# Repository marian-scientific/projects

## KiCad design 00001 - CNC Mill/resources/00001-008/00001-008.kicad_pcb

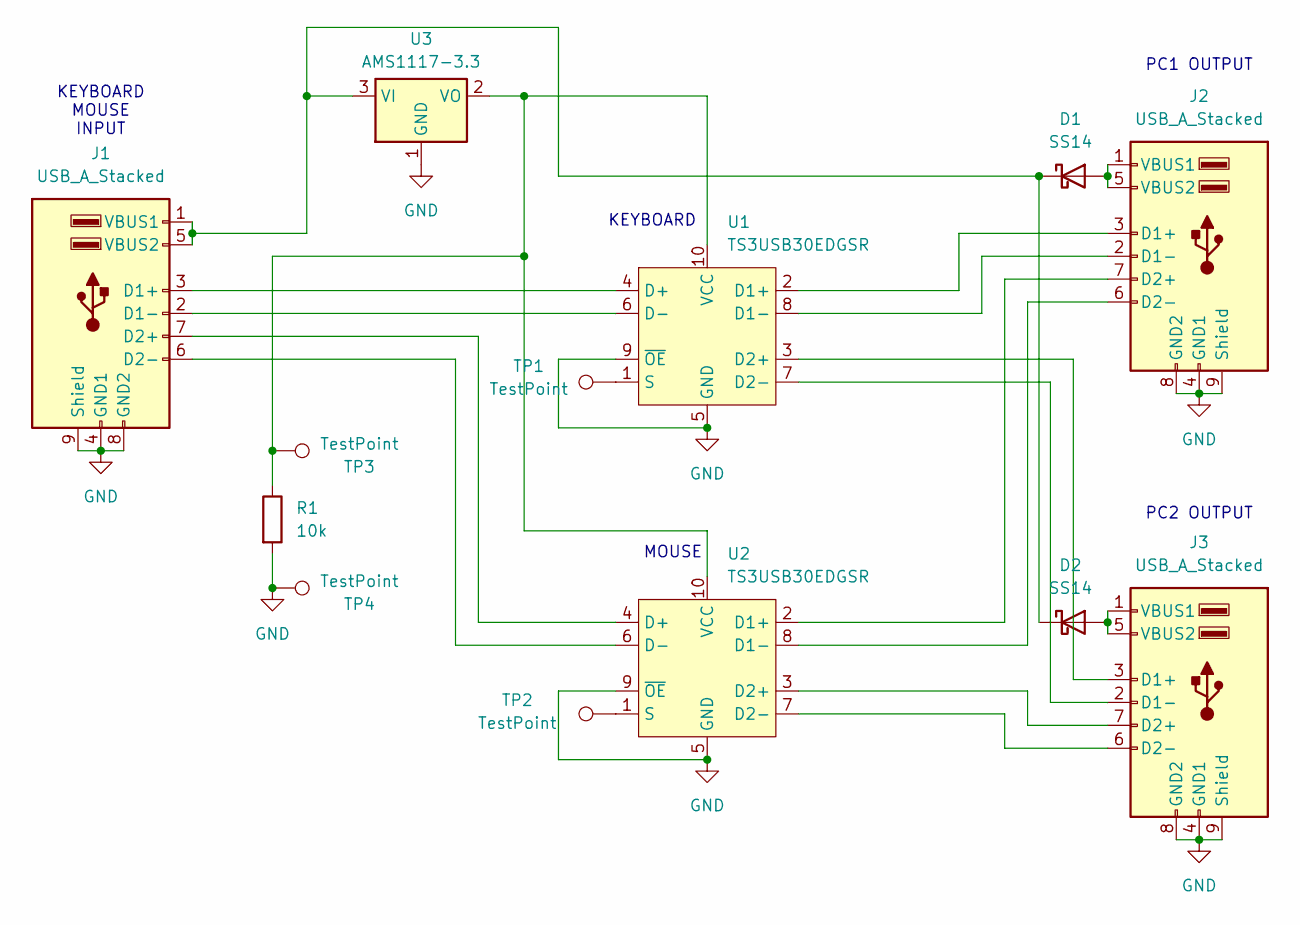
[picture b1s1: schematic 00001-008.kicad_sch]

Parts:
D1, D2: SS14; D_SMA
J1, J2, J3: USB_A_Stacked; USB_A_CUI_UJ2-ADH-TH_Horizontal_Stacked
R1: 10k; R_1206_3216Metric
TP1, TP2, TP3, TP4: TestPoint; TestPoint_Pad_3.0x3.0mm
U1, U2: TS3USB30EDGSR; VSSOP-10_3x3mm_P0.5mm
U3: AMS1117-3.3; SOT-223-3_TabPin2

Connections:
GND: J1.4 (GND1), J1.8 (GND2), J1.9 (Shield), J2.4 (GND1), J2.8 (GND2), J2.9 (Shield), J3.4 (GND1), J3.8 (GND2), J3.9 (Shield), R1.2, TP4.1, U1.5 (GND), U1.9 (~OE), U2.5 (GND), U2.9 (~OE), U3.1 (GND)
unnamed: D1.2 (A), J2.1 (VBUS1), J2.5 (VBUS2)
unnamed: D1.1 (K), D2.1 (K), J1.1 (VBUS1), J1.5 (VBUS2), U3.3 (VI)
unnamed: D2.2 (A), J3.1 (VBUS1), J3.5 (VBUS2)
unnamed: J1.3 (D1+), U1.4 (D+)
unnamed: J1.2 (D1-), U1.6 (D-)
unnamed: J1.7 (D2+), U2.4 (D+)
unnamed: J1.6 (D2-), U2.6 (D-)
unnamed: J2.3 (D1+), U1.2 (D1+)
unnamed: J2.2 (D1-), U1.8 (D1-)
unnamed: J2.7 (D2+), U2.2 (D1+)
unnamed: J2.6 (D2-), U2.8 (D1-)
unnamed: J3.3 (D1+), U1.3 (D2+)
unnamed: J3.2 (D1-), U1.7 (D2-)
unnamed: J3.7 (D2+), U2.3 (D2+)
unnamed: J3.6 (D2-), U2.7 (D2-)
unnamed: TP1.1, U1.1 (S)
unnamed: R1.1, TP3.1, U1.10 (VCC), U2.10 (VCC), U3.2 (VO)
unnamed: TP2.1, U2.1 (S)

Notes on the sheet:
PC1 OUTPUT
KEYBOARD MOUSE INPUT
PC2 OUTPUT
KEYBOARD
MOUSE

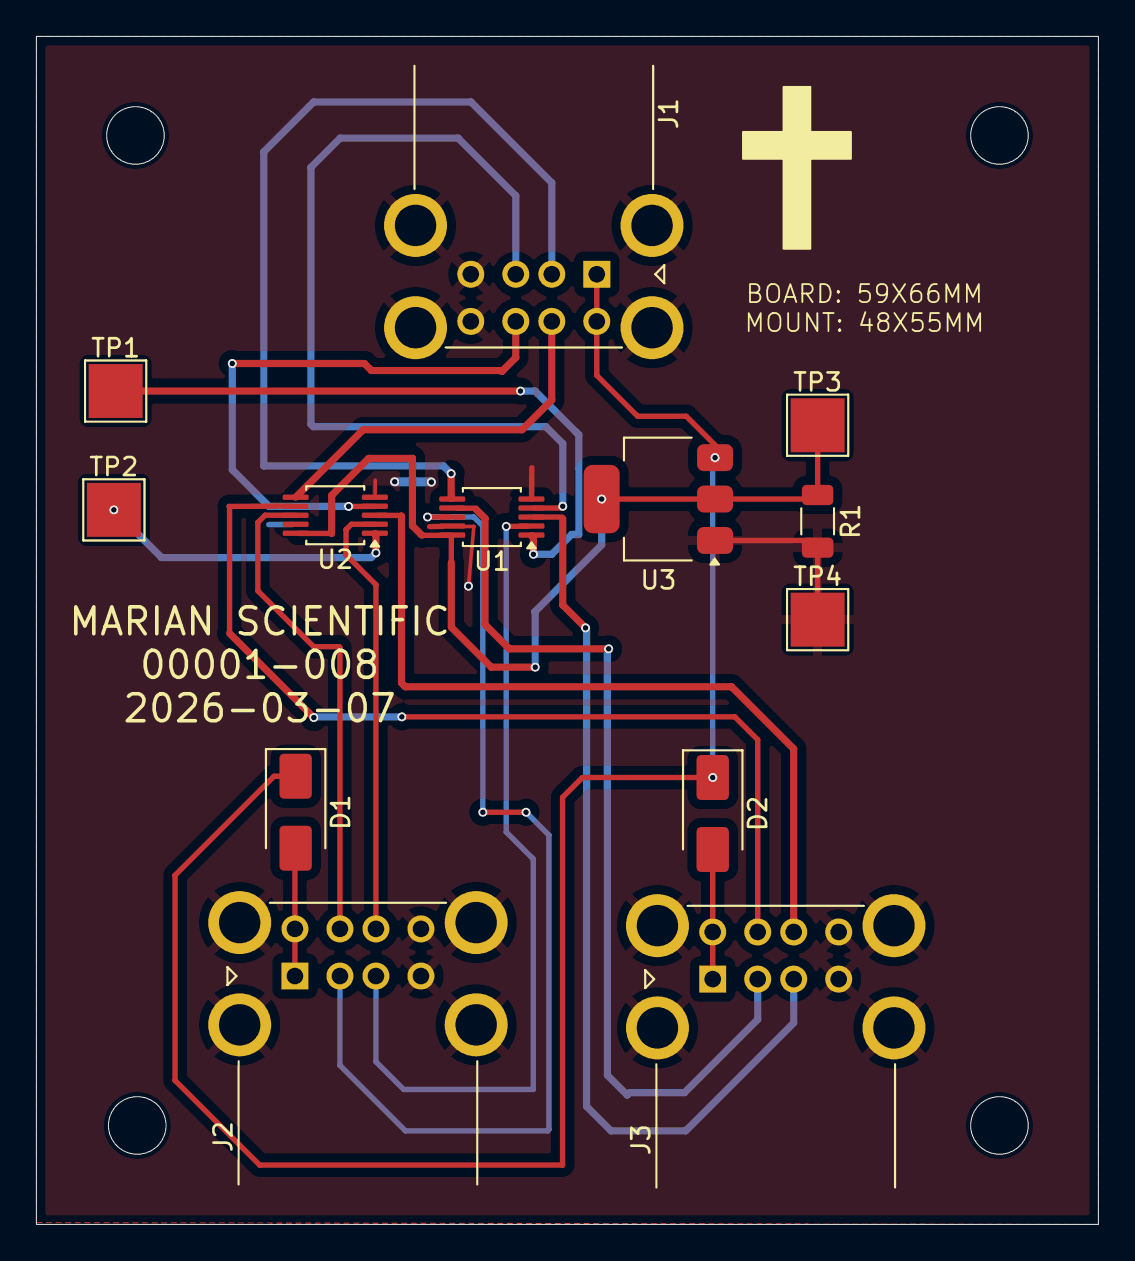
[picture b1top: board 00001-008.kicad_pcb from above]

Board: 2 copper layers, 59.0 x 66.0 mm, 13 parts (0 on the bottom side), 19 nets.

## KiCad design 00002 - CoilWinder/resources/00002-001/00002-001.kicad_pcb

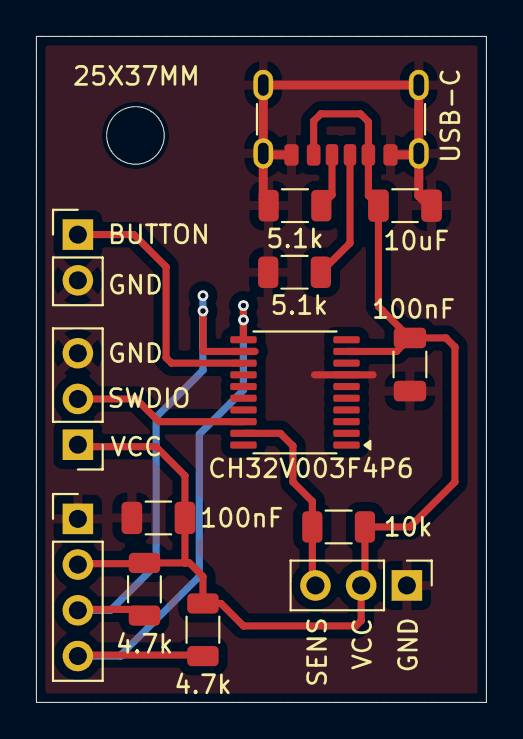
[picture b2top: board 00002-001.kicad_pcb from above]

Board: 2 copper layers, 25.0 x 37.0 mm, 14 parts (0 on the bottom side), 9 nets.

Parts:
4.7k, 4.7k#2: 4.7k; R_1206_3216Metric
5.1k, 5.1k#2: 5.1k; R_1206_3216Metric
10k: 10k; R_1206_3216Metric
10uF: 10uF; C_1206_3216Metric
100nF, 100nF#2: .1uF; C_1206_3216Metric
CH32V003F4P6: CH32V003FxPx; TSSOP-20_4.4x6.5mm_P0.65mm
J2: Conn_01x04_Pin; PinHeader_1x04_P2.54mm_Vertical
J3, J5: Conn_01x03_Pin; PinHeader_1x03_P2.54mm_Vertical
J4: Conn_01x02_Pin; PinHeader_1x02_P2.54mm_Vertical
USB-C: USB_C_Receptacle_PowerOnly_6P; USB_C_Receptacle_GCT_USB4125-xx-x_6P_TopMnt_Horizontal

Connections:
+5V: 4.7k.2, 4.7k#2.2, 10k.2, 10uF.1, 100nF.1, 100nF#2.1, CH32V003F4P6.9 (VDD), J2.2, J3.2, J5.1, USB-C.A9 (VBUS), USB-C.B9 (VBUS)
GND: 5.1k.2, 5.1k#2.2, 10uF.2, 100nF.2, 100nF#2.2, CH32V003F4P6.7 (VSS), J2.1, J3.1, J4.2, J5.3, USB-C.A12 (GND), USB-C.B12 (GND), USB-C.S1 (SHIELD)
unnamed: 5.1k.1, USB-C.A5 (CC1)
unnamed: 5.1k#2.1, USB-C.B5 (CC2)
unnamed: 4.7k#2.1, CH32V003F4P6.12 (PC2), J2.3
unnamed: 4.7k.1, CH32V003F4P6.11 (PC1), J2.4
unnamed: 10k.1, CH32V003F4P6.19 (PD2), J3.3
unnamed: CH32V003F4P6.13 (PC3), J4.1
unnamed: CH32V003F4P6.18 (PD1), J5.2

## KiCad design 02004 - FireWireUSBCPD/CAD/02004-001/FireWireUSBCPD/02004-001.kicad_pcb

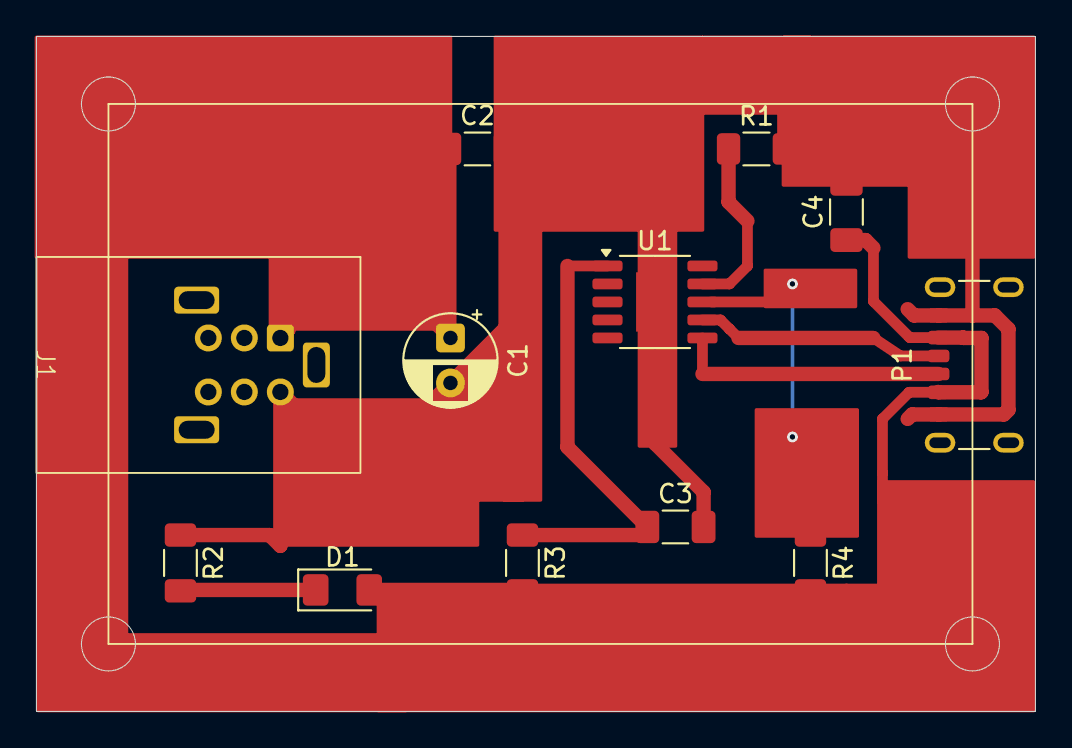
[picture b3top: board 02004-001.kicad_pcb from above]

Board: 2 copper layers, 55.5 x 37.5 mm, 12 parts (0 on the bottom side), 7 nets.

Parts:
C1: 22uF; CP_Radial_D5.0mm_P2.50mm
C2: 0.1uF; C_1206_3216Metric_Pad1.33x1.80mm_HandSolder
C3: 1uF; C_1206_3216Metric_Pad1.33x1.80mm_HandSolder
C4: 10uF; C_1206_3216Metric_Pad1.33x1.80mm_HandSolder
D1: LED; LED_1206_3216Metric_Pad1.42x1.75mm_HandSolder
J1: IEEE1394a; IEEE1394 930
P1: USB_C_Plug_USB2.0; USB_C_Receptacle_GCT_USB4125-xx-x_6P_TopMnt_Horizontal
R1: 56K; R_1206_3216Metric_Pad1.30x1.75mm_HandSolder
R2: 2K; R_1206_3216Metric_Pad1.30x1.75mm_HandSolder
R3: 1K; R_1206_3216Metric_Pad1.30x1.75mm_HandSolder
R4: 10K; R_1206_3216Metric_Pad1.30x1.75mm_HandSolder
U1: CH224K; SSOP-10-1EP_3.9x4.9mm_P1mm_EP2.1x3.3mm

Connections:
GND: C1.2, C2.2, C3.2, C4.2, J1.2 (GND), P1.A12 (GND), P1.B12 (GND), R1.2, R2.1, U1.11 (GND)
unnamed: C1.1, C2.1, C4.1, D1.2 (A), J1.1 (PWR), P1.A9 (VBUS), P1.B9 (VBUS), R3.2, R4.2
unnamed: D1.1 (K), R2.2
unnamed: P1.A5 (CC), U1.6 (CC2), U1.7 (CC1)
unnamed: R1.1, U1.9 (CFG1)
unnamed: R4.1, U1.8 (VBUS)
unnamed: C3.1, R3.1, U1.1 (VDD)

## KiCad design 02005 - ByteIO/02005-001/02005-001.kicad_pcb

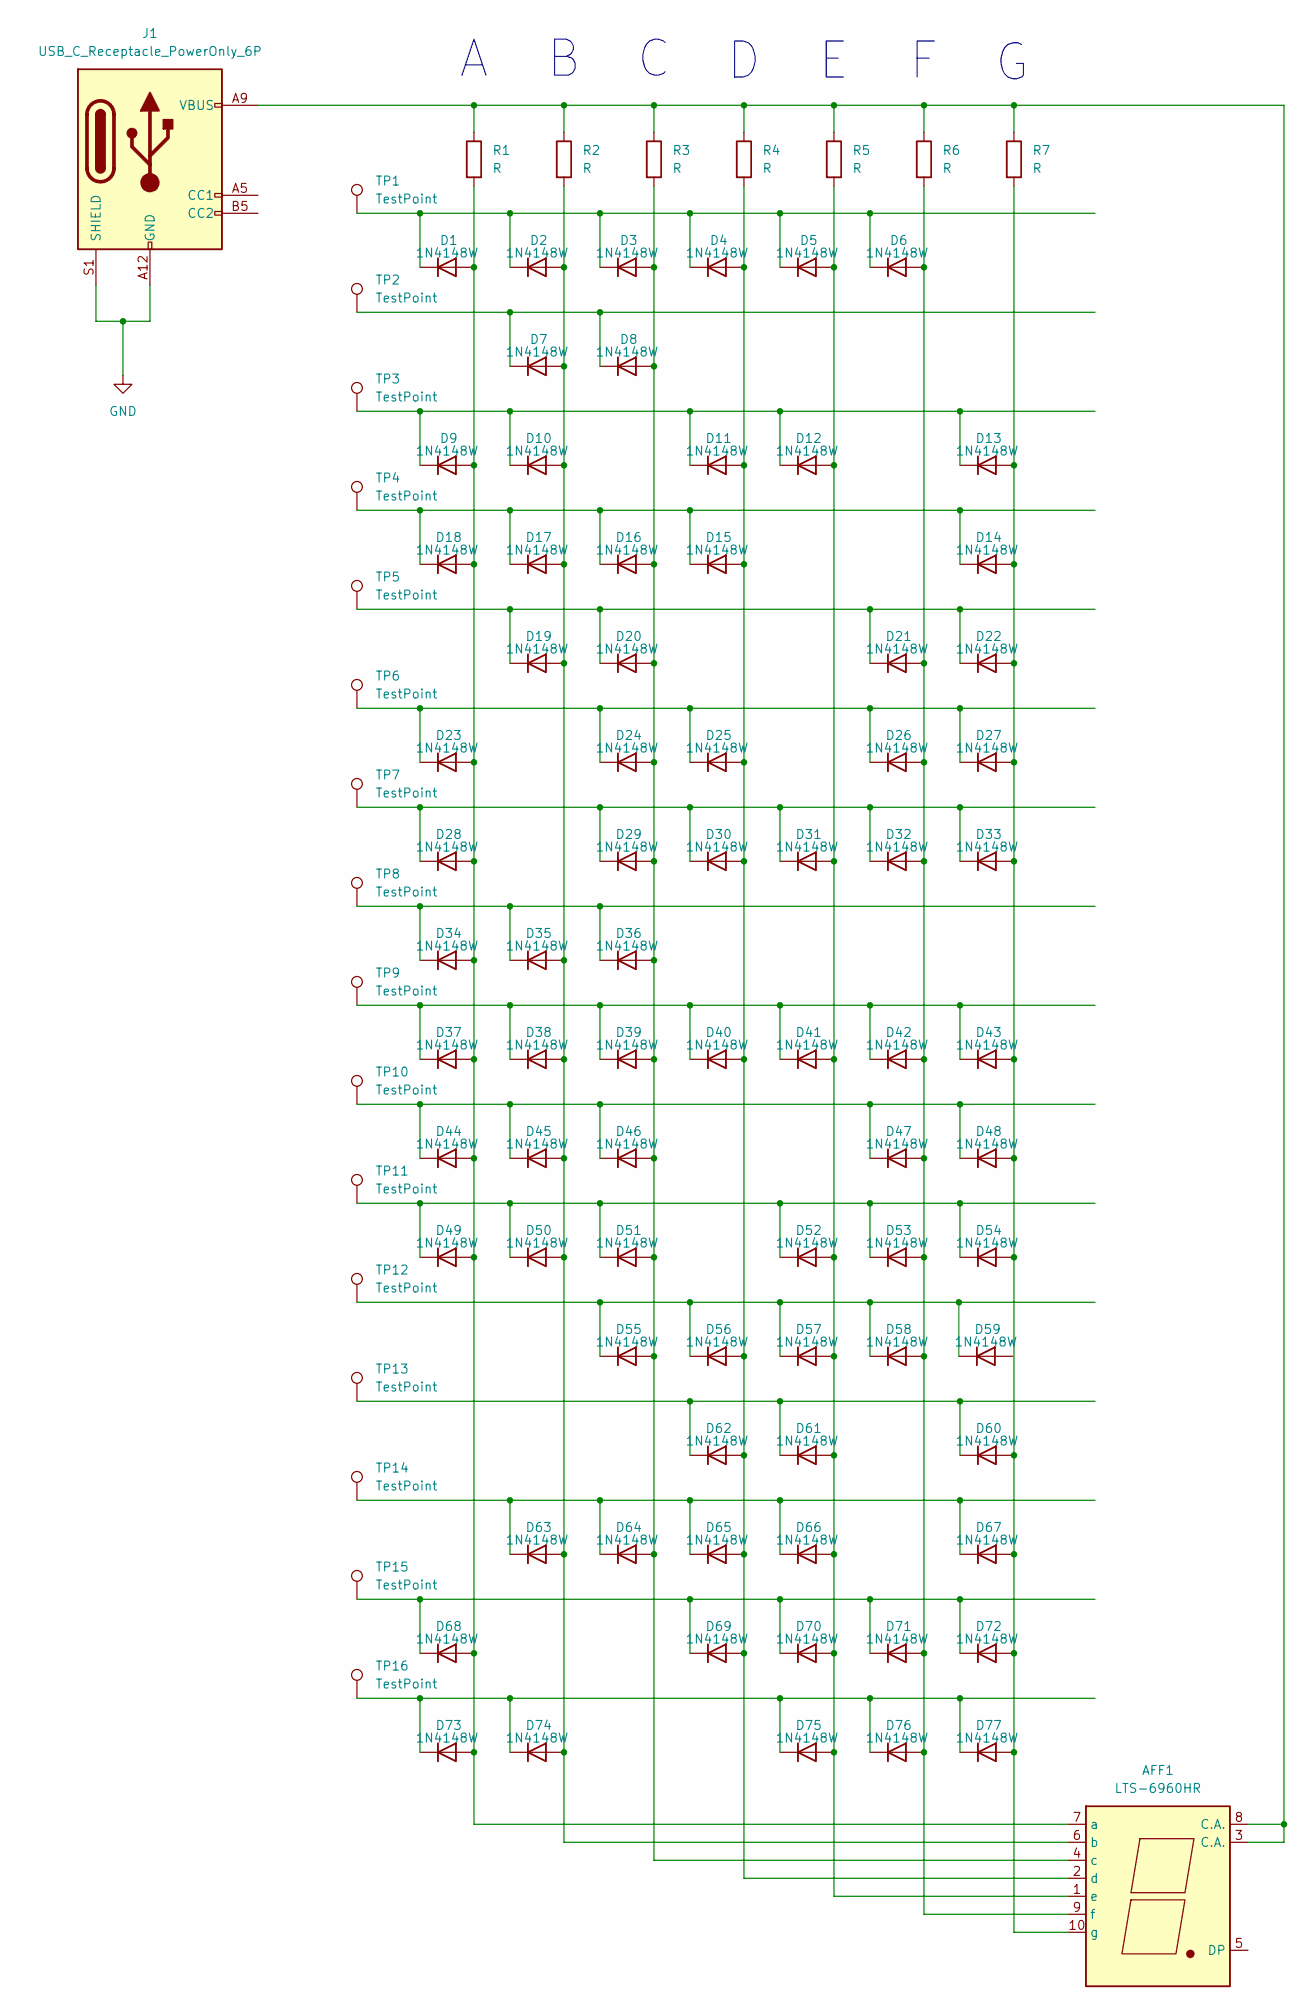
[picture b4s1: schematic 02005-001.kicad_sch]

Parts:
AFF1: LTS-6960HR; 7SegmentLED_LTS6760_LTS6780
D1, D2, D3, D4, D5, D6, D7, D8, D9, D10, D11, D12, D13, D14, D15, D16, D17, D18, D19, D20, D21, D22, D23, D24, D25, D26, D27, D28, D29, D30, D31, D32, D33, D34, D35, D36, D37, D38, D39, D40, D41, D42, D43, D44, D45, D46, D47, D48, D49, D50, D51, D52, D53, D54, D55, D56, D57, D58, D59, D60, D61, D62, D63, D64, D65, D66, D67, D68, D69, D70, D71, D72, D73, D74, D75, D76, D77: 1N4148W; D_SOD-123
J1: USB_C_Receptacle_PowerOnly_6P; USB_C_Receptacle_GCT_USB4125-xx-x_6P_TopMnt_Horizontal
R1, R2, R3, R4, R5, R6, R7: R; R_1206_3216Metric
TP1, TP2, TP3, TP4, TP5, TP6, TP7, TP8, TP9, TP10, TP11, TP12, TP13, TP14, TP15, TP16: TestPoint; TestPoint_Pad_4.0x4.0mm

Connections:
GND: J1.A12 (GND), J1.B12 (GND), J1.S1 (SHIELD)
unnamed: AFF1.3 (C.A.), AFF1.8 (C.A.), J1.A9 (VBUS), J1.B9 (VBUS), R1.1, R2.1, R3.1, R4.1, R5.1, R6.1, R7.1
unnamed: AFF1.7 (a), D1.2 (A), D9.2 (A), D18.2 (A), D23.2 (A), D28.2 (A), D34.2 (A), D37.2 (A), D44.2 (A), D49.2 (A), D68.2 (A), D73.2 (A), R1.2
unnamed: AFF1.6 (b), D2.2 (A), D7.2 (A), D10.2 (A), D17.2 (A), D19.2 (A), D35.2 (A), D38.2 (A), D45.2 (A), D50.2 (A), D63.2 (A), D74.2 (A), R2.2
unnamed: AFF1.4 (c), D3.2 (A), D8.2 (A), D16.2 (A), D20.2 (A), D24.2 (A), D29.2 (A), D36.2 (A), D39.2 (A), D46.2 (A), D51.2 (A), D55.2 (A), D64.2 (A), R3.2
unnamed: AFF1.2 (d), D4.2 (A), D11.2 (A), D15.2 (A), D25.2 (A), D30.2 (A), D40.2 (A), D56.2 (A), D62.2 (A), D65.2 (A), D69.2 (A), R4.2
unnamed: AFF1.1 (e), D5.2 (A), D12.2 (A), D31.2 (A), D41.2 (A), D52.2 (A), D57.2 (A), D61.2 (A), D66.2 (A), D70.2 (A), D75.2 (A), R5.2
unnamed: AFF1.9 (f), D6.2 (A), D21.2 (A), D26.2 (A), D32.2 (A), D42.2 (A), D47.2 (A), D53.2 (A), D58.2 (A), D71.2 (A), D76.2 (A), R6.2
unnamed: AFF1.10 (g), D13.2 (A), D14.2 (A), D22.2 (A), D27.2 (A), D33.2 (A), D43.2 (A), D48.2 (A), D54.2 (A), D60.2 (A), D67.2 (A), D72.2 (A), D77.2 (A), R7.2
unnamed: D1.1 (K), D2.1 (K), D3.1 (K), D4.1 (K), D5.1 (K), D6.1 (K), TP1.1
unnamed: D7.1 (K), D8.1 (K), TP2.1
unnamed: D9.1 (K), D10.1 (K), D11.1 (K), D12.1 (K), D13.1 (K), TP3.1
unnamed: D14.1 (K), D15.1 (K), D16.1 (K), D17.1 (K), D18.1 (K), TP4.1
unnamed: D19.1 (K), D20.1 (K), D21.1 (K), D22.1 (K), TP5.1
unnamed: D23.1 (K), D24.1 (K), D25.1 (K), D26.1 (K), D27.1 (K), TP6.1
unnamed: D28.1 (K), D29.1 (K), D30.1 (K), D31.1 (K), D32.1 (K), D33.1 (K), TP7.1
unnamed: D34.1 (K), D35.1 (K), D36.1 (K), TP8.1
unnamed: D37.1 (K), D38.1 (K), D39.1 (K), D40.1 (K), D41.1 (K), D42.1 (K), D43.1 (K), TP9.1
unnamed: D44.1 (K), D45.1 (K), D46.1 (K), D47.1 (K), D48.1 (K), TP10.1
unnamed: D49.1 (K), D50.1 (K), D51.1 (K), D52.1 (K), D53.1 (K), D54.1 (K), TP11.1
unnamed: D55.1 (K), D56.1 (K), D57.1 (K), D58.1 (K), D59.1 (K), TP12.1
unnamed: D60.1 (K), D61.1 (K), D62.1 (K), TP13.1
unnamed: D63.1 (K), D64.1 (K), D65.1 (K), D66.1 (K), D67.1 (K), TP14.1
unnamed: D68.1 (K), D69.1 (K), D70.1 (K), D71.1 (K), D72.1 (K), TP15.1
unnamed: D73.1 (K), D74.1 (K), D75.1 (K), D76.1 (K), D77.1 (K), TP16.1

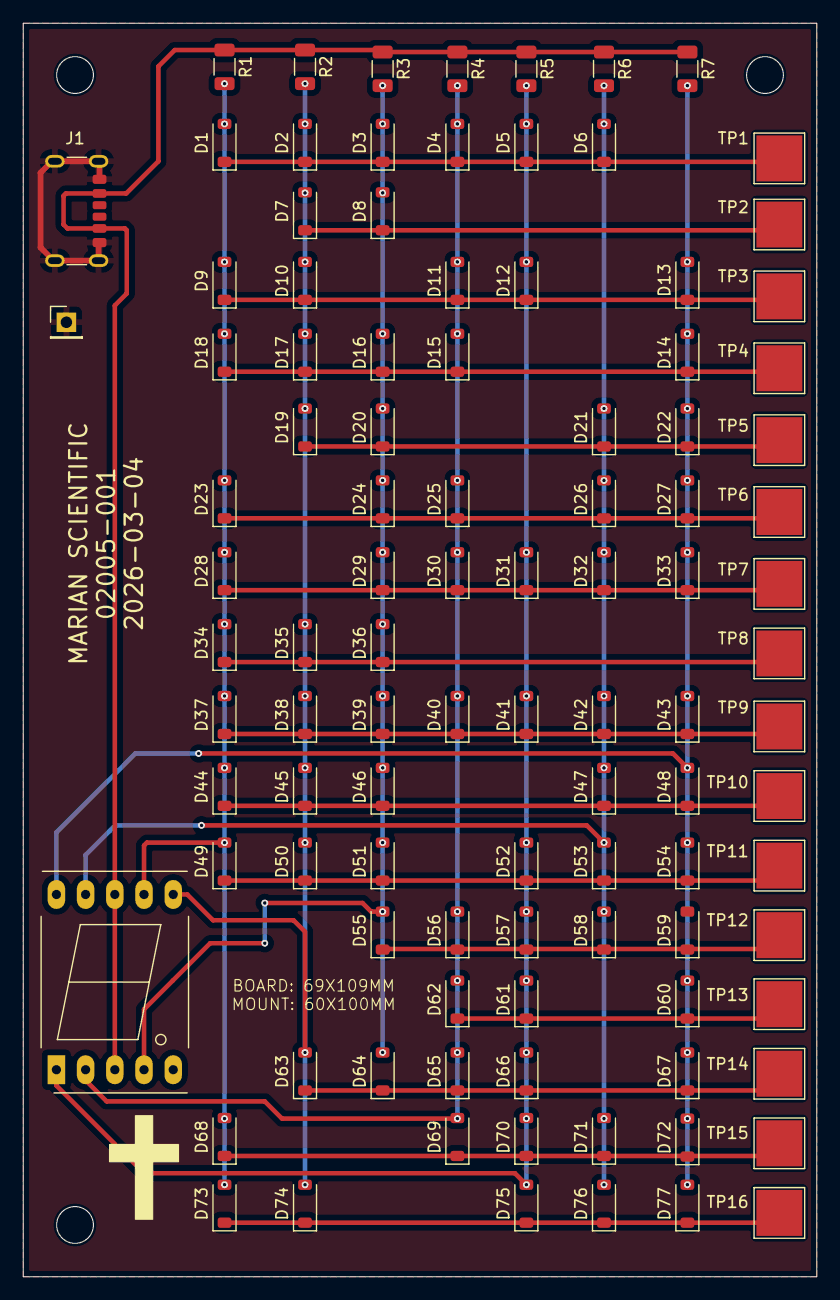
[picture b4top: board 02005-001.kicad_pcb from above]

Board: 2 copper layers, 69.0 x 109.0 mm, 102 parts (0 on the bottom side), 25 nets.
